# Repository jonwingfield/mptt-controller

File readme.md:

# MPTT Charge Controller

Reference Design: http://www.ti.com/tool/TIDA-00120

Better Reference Design: http://www.ti.com/lit/ug/tiduej8a/tiduej8a.pdf?&ts=1588978099192

## Resources

- How Buck Converters work (video is super helpful): https://electronicsforu.com/videos-slideshows/diy-buck-converter-tutorial
- DIY MPTT Charge Controller: http://coder-tronics.com/c2000-solar-mppt-tutorial-pt1/. This explains how to build a buck converter that is very efficient (see notes below).
- Fundamentals of MOSFET Driver circuits: http://www.ti.com/lit/ml/slua618/slua618.pdf
- Another DIY. Very mature https://hackaday.io/project/158859-high-efficiency-mppt-solar-charger
- TI Buck Converter Reference: http://www.ti.com/tool/PMP7051C http://www.ti.com/lit/ug/sluu121b/sluu121b.pdf

## Theory of Operation

### Buck Converter

The basics of a buck converter are simple and are well-explained in the above link. Use PWM and a MOSFET to reduce the average voltage. Add an inductor to smooth the current. Add a diode to create a current path when the MOSFET is off. Add a capacitor to smooth the voltage. Finally, some voltage feedback mechanism is necessary to adapt the PWM duty cycle to keep the voltage constant.

#### Component Selection (Inductor and Capacitor)

http://www.onsemi.com/pub/Collateral/AND9135-D.PDF
http://www.ti.com/lit/an/snva038b/snva038b.pdf?ts=1591102835925

#### Efficiency (see resources for overview)

Efficiency Calculation: http://www.ti.com/lit/an/slyt358/slyt358.pdf and https://www.electronicdesign.com/power/fundamentals-buck-converter-efficiency

There a few efficiency problems with the basic buck converter design:

1. The voltage drop of the diode.
2. Output ripple.
3. Switching losses in the MOSFET.

(1) is addressed by replacing the diode with a MOSFET and toggling it opposite the main MOSFET. The main MOSFET is known as the high-side and the other is the low-side. This is called a synchronous buck converter.
(2) is addressed by what's known as an *interleaved* design. This places two circuits in parallel, which supposedly halves the ripple. _TODO: understand why_.
(3) is minimized by a few factors:
1. Low RDS(on) MOSFET.
2. Low Rise/Fall time MOSFET.
3. Selection of switch frequency. A higher frequency will reduce output ripple but increase switching losses, and vise-versa.

Another important consideration is the drive current of the gate driver IC. A higher drive current will switch the MOSFET faster and result in lower switching losses. _TODO: understand why_

### Ringing

http://www.ti.com/lit/an/slpa010/slpa010.pdf

This happens at the gate of the MOSFETs. I don't fully understand why yet, even after reading the above, but it's the reason we need a gate resistor between the driver and the MOSFET.

Also, parasitic inductances and capacitances occur due to the fast switching, so an RC Snubber circuit can be used to mitigate this: http://rohmfs.rohm.com/en/products/databook/applinote/ic/power/switching_regulator/buck_snubber_app-e.pdf

Techniques to reduce ringing: http://www.ti.com/lit/an/slpa010/slpa010.pdf

## Diode Emulation Mode

When the current is low, the inductor current can go negative, resulting in lost efficiency and back current flow into the panel. To prevent this, the sync FET is kept off and uses the body diode to conduct current. This is known as diode emulation mode. 

Important: we also need to use this mode at startup to prevent issues with reverse current flow. See https://en-support.renesas.com/knowledgeBase/4967491. 

See also: http://www.ti.com/lit/ug/tiduan2/tiduan2.pdf?ts=1590949279905

## Appendix A - Notes (because I'm a noob ;)

N-Channel MOSFETs/Transistors are generally used on the ground side of a load. P-Channels on the high side, and are reversed (low = on, high = off).

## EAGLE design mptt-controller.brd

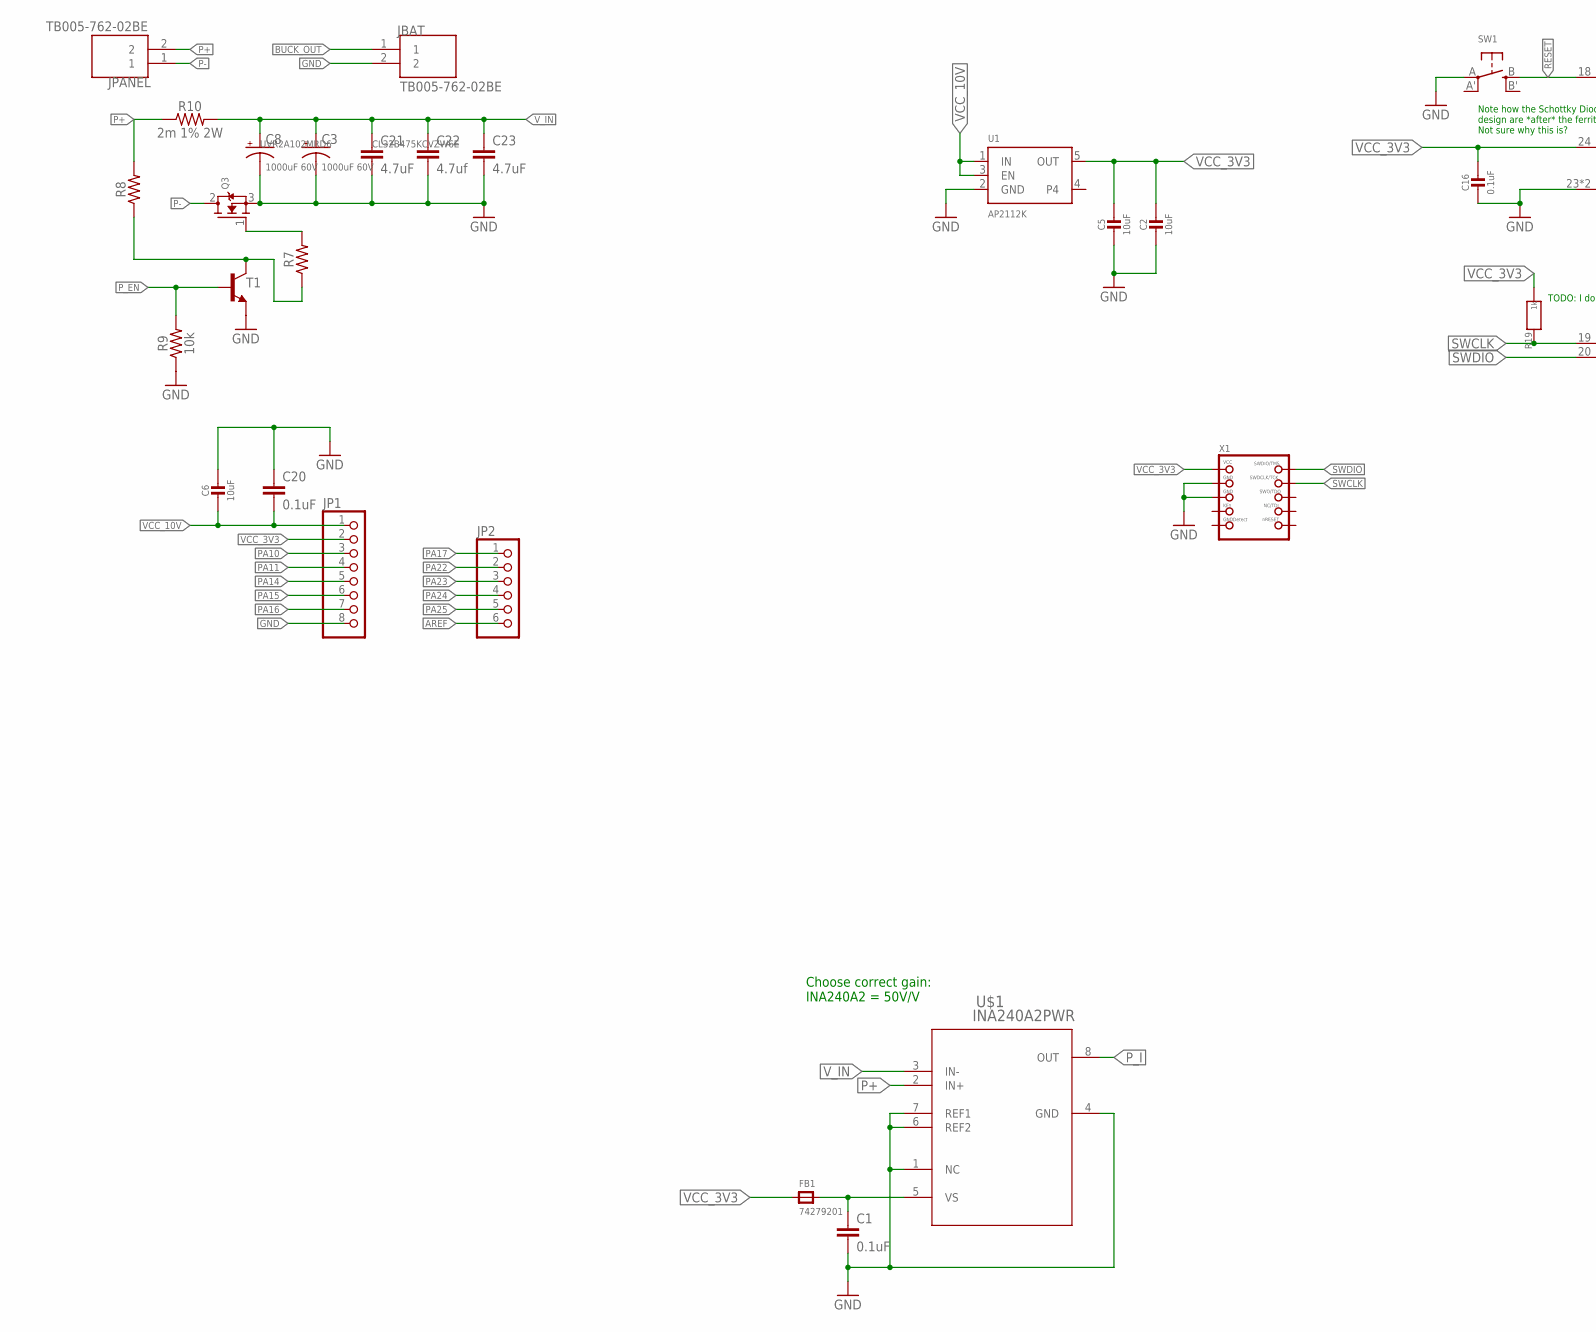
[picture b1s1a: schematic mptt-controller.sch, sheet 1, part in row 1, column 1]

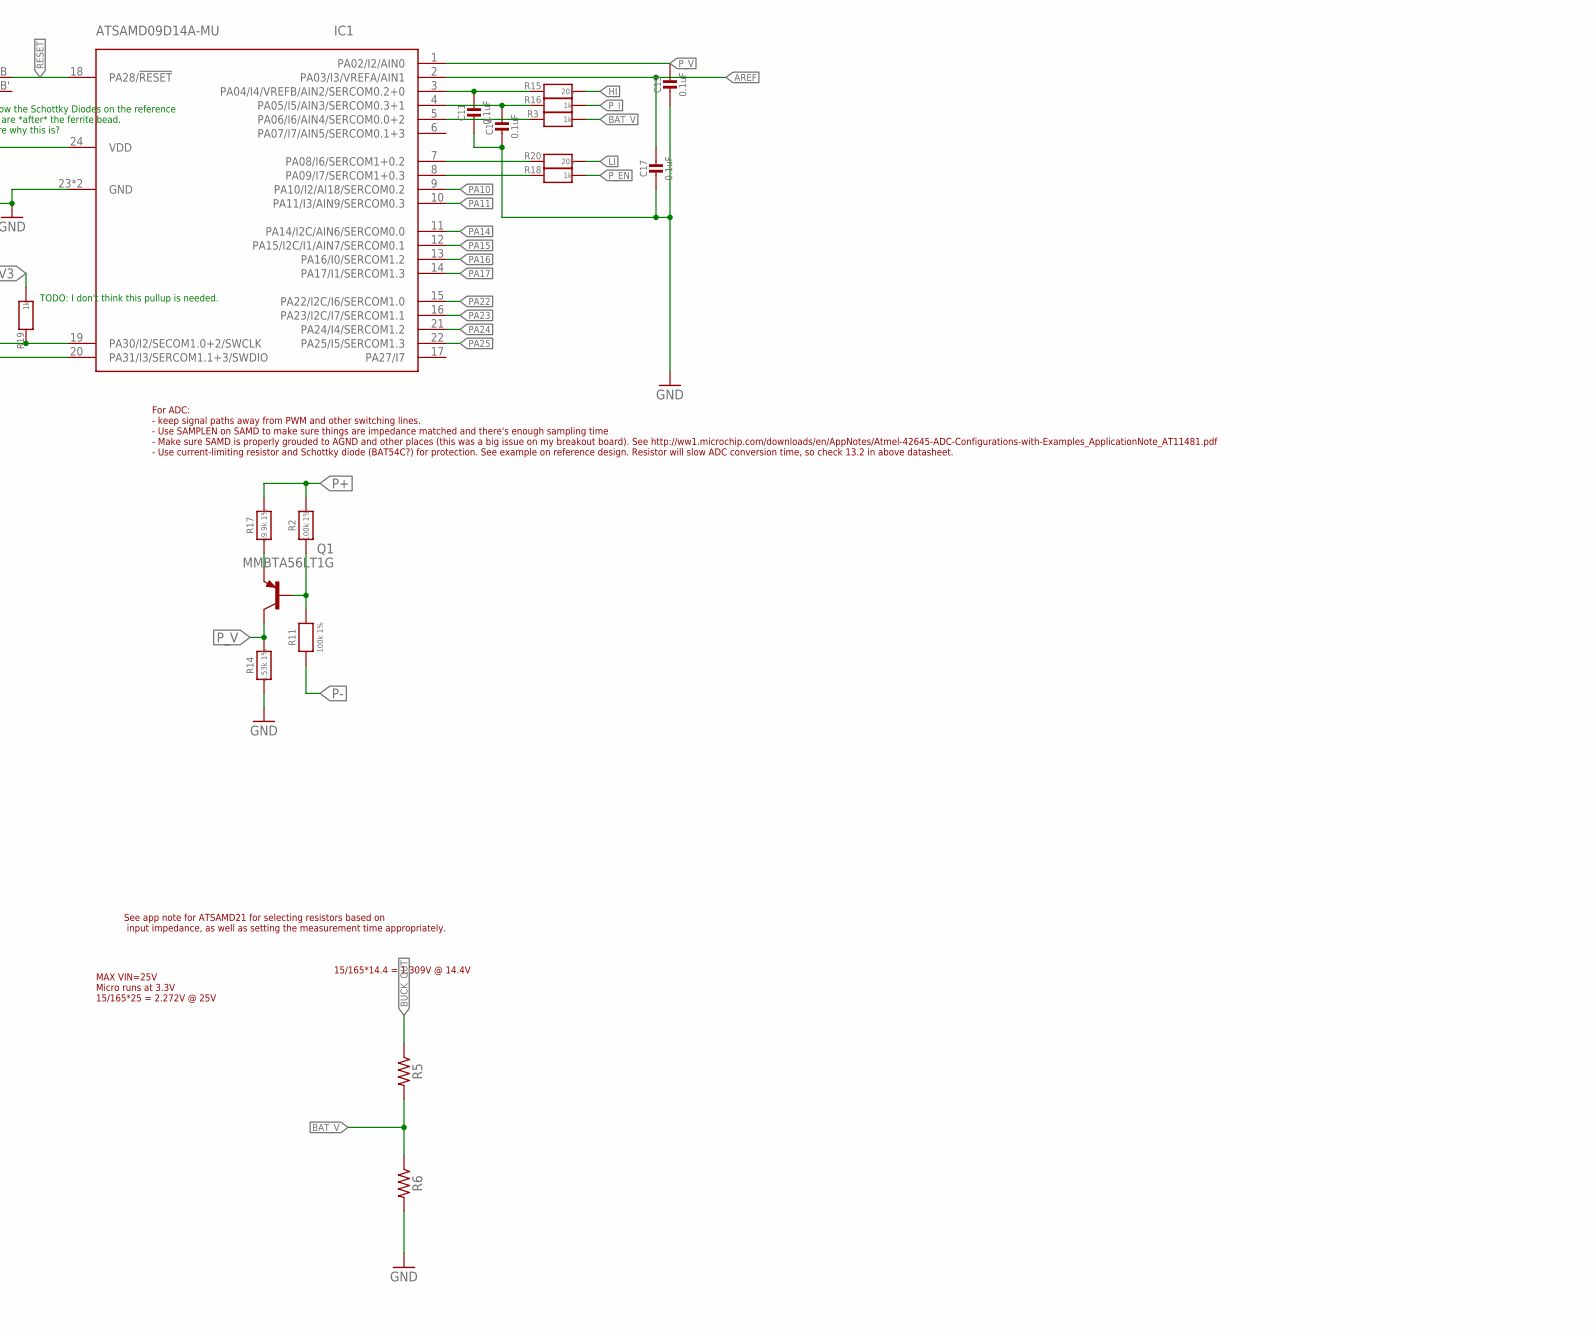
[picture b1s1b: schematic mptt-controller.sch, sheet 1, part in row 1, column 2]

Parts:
C1, C20: 0.1uF; 0603-CAP
C2, C5, C6: 10uF; _0805
C3: 1000uF 60V; CPOL-RADIAL-1000UF-25V
C8: 1000uF 60V; CPOL-RADIAL-1000UF-25V; PARTNUM UVR2A102MRD6
C11, C13, C14, C16, C17: 0.1uF; _0402MP
C21: 4.7uF; C1210; PARTNUM CL32B475KCVZW6E
C22: 4.7uf; C1210
C23: 4.7uF; C1210
FB1: 74279201; _0805
IC1: ATSAMD09D14A-MU; QFN24_4MM
JBAT: TB005-762-02BE; CUI_TB005-762-02BE
JP1: HEADER-1X8ROUND; 1X08_ROUND
JP2: HEADER-1X6ROUND; 1X06_ROUND
JPANEL: TB005-762-02BE; CUI_TB005-762-02BE
Q1: MMBTA56LT1G; SOT23-BEC
Q3: MOSFET-NGDS_TO220V; TO220V
R2, R11: 100k 1%; _0805MP
R3, R16, R18, R19: 1k; _0402MP
R5, R6, R7, R8: 0603
R9: 10k; 0603
R10: 2m 1% 2W; 2512
R14: 4.53k 1%; _0805MP
R15, R20: 205; _0402MP
R17: 49.9k 1%; _0805MP
SW1: SWITCH_TACT_SMT4.6X2.8; BTN_KMR2_4.6X2.8
T1: MMBT3904LT1-NPN-SOT23-BEC; SOT23-BEC
U1: AP2112K; SOT23-5
U$1: INA240A2PWR; PW0008A_N
X1: JTAG-CORTEXBOX; 2X05_1.27MM_BOX_NOPOSTS

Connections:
AREF: C17.1, IC1.2 (PA03/I3/VREFA/AIN1), JP2.6
BAT_V: R3.2, R5.2, R6.1
BUCK_OUT: JBAT.1, R5.1; also elsewhere on the board
GND: C1.2, C2.2, C3.-, C5.2, C6.1, C8.-, C11.2, C13.2, C14.2, C16.2, C17.2, C20.1, C21.2, C22.2, C23.2, IC1.23 (GND), IC1.THERM (GND), JBAT.2, JP1.8, Q3.3 (S), R6.2, R9.1, R14.1, SW1.A, T1.E, U1.2 (GND), U$1.1 (NC), U$1.4 (GND), U$1.6 (REF2), U$1.7 (REF1), X1.3 (GND), X1.5 (GND); also elsewhere on the board
HI: R15.2; also elsewhere on the board
LI: R20.2; also elsewhere on the board
unnamed: IC1.7 (PA08/I6/SERCOM1+0.2), R20.1
unnamed: Q3.1 (G), R7.2
unnamed: IC1.8 (PA09/I7/SERCOM1+0.3), R18.1
unnamed: Q1.B, R2.1, R11.2
unnamed: Q1.E, R17.1
unnamed: C11.1, IC1.3 (PA04/I4/VREFB/AIN2/SERCOM0.2+0), R15.1
unnamed: R7.1, R8.1, T1.C
unnamed: C14.1, IC1.4 (PA05/I5/AIN3/SERCOM0.3+1), R16.1
unnamed: IC1.5 (PA06/I6/AIN4/SERCOM0.0+2), R3.1
P+: JPANEL.2, R2.2, R8.2, R10.P$1 (1), R17.2, U$1.2 (IN+)
P-: JPANEL.1, Q3.2 (D), R11.1
PA10: IC1.9 (PA10/I2/AI18/SERCOM0.2), JP1.3
PA11: IC1.10 (PA11/I3/AIN9/SERCOM0.3), JP1.4
PA14: IC1.11 (PA14/I2C/AIN6/SERCOM0.0), JP1.5
PA15: IC1.12 (PA15/I2C/I1/AIN7/SERCOM0.1), JP1.6
PA16: IC1.13 (PA16/I0/SERCOM1.2), JP1.7
PA17: IC1.14 (PA17/I1/SERCOM1.3), JP2.1
PA22: IC1.15 (PA22/I2C/I6/SERCOM1.0), JP2.2
PA23: IC1.16 (PA23/I2C/I7/SERCOM1.1), JP2.3
PA24: IC1.21 (PA24/I4/SERCOM1.2), JP2.4
PA25: IC1.22 (PA25/I5/SERCOM1.3), JP2.5
P_EN: R9.2, R18.2, T1.B
P_I: R16.2, U$1.8 (OUT)
P_V: C13.1, IC1.1 (PA02/I2/AIN0), Q1.C, R14.2
RESET: IC1.18 (PA28/!RESET), SW1.B (S)
SWCLK: IC1.19 (PA30/I2/SECOM1.0+2/SWCLK), R19.1, X1.4 (SWDCLK)
SWDIO: IC1.20 (PA31/I3/SERCOM1.1+3/SWDIO), X1.2 (SWDIO)
VCC_3V3: C2.1, C5.1, C16.1, FB1.1, IC1.24 (VDD), JP1.2, R19.2, U1.5 (OUT), X1.1 (VCC)
VCC_10V: C6.2, C20.2, JP1.1, U1.1 (IN), U1.3 (EN); also elsewhere on the board
VS: C1.1, FB1.2, U$1.5 (VS)
V_IN: C3.+, C8.+, C21.1, C22.1, C23.1, R10.P$2 (2), U$1.3 (IN-); also elsewhere on the board

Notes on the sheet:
For ADC: - keep signal paths away from PWM and other switching lines. - Use SAMPLEN on SAMD to make sure things are impedance matched and there's enough sampling time - Make sure SAMD is properly grouded to AGND and other places (this was a big issue on my breakout board). See http://ww1.microchip.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
MAX VIN=25V Micro runs at 3.3V 15/165*25 = 2.272V @ 25V
15/165*14.4 = 1.309V @ 14.4V
See app note for ATSAMD21 for selecting resistors based on input impedance, as well as setting the measurement time appropriately.
Choose correct gain: INA240A2 = 50V/V
Note how the Schottky Diodes on the reference design are *after* the ferrite bead. Not sure why this is?
TODO: I don't think this pullup is needed.

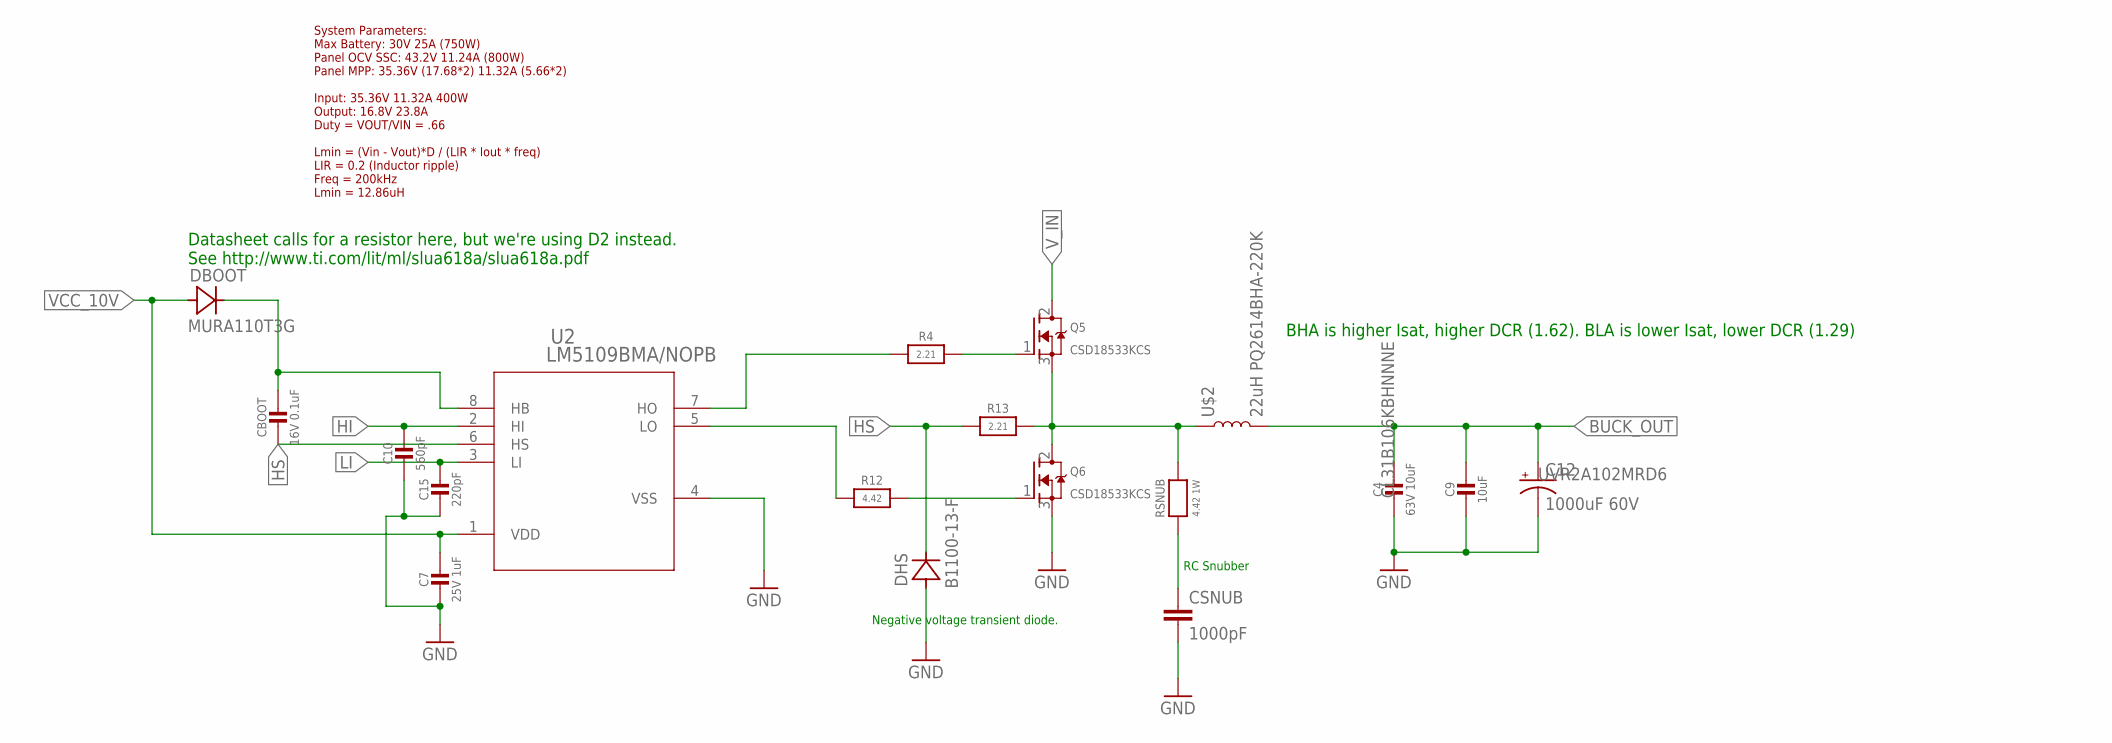
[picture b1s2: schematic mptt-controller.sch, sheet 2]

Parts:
C4: 63V 10uF; _1206
C7: 25V 1uF; _0805
C9: 10uF; _1206
C10: 560pF; _0603
C12: 1000uF 60V; CPOL-RADIAL-1000UF-25V; PARTNUM UVR2A102MRD6
C15: 220pF; _0603
CBOOT: 16V 0.1uF; _0805
CSNUB: 1000pF; 0603-CAP
DBOOT: MURA110T3G; SMA
DHS: B1100-13-F; SMA
Q5, Q6: CSD18533KCS; TO220V
R4, R13: 2.21; _0805
R12: 4.42; _0805
RSNUB: 4.42 1W; 2512
U2: LM5109BMA/NOPB; M08A_TEX
U$2: 22uH PQ2614BHA-220K; PQ2614

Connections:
BUCK_OUT: C4.1, C9.1, C12.+, U$2.P2 (2); also elsewhere on the board
GND: C4.2, C7.2, C9.2, C10.2, C12.-, C15.2, CSNUB.2, DHS.A, Q6.3 (S), U2.4 (VSS); also elsewhere on the board
HB: CBOOT.1, DBOOT.C, U2.8 (HB)
HI: C10.1, U2.2 (HI); also elsewhere on the board
HO: R4.1, U2.7 (HO)
HS: CBOOT.2, DHS.C, R13.1, U2.6 (HS)
LI: C15.1, U2.3 (LI); also elsewhere on the board
LO: R12.1, U2.5 (LO)
unnamed: Q5.1 (G), R4.2
unnamed: CSNUB.1, RSNUB.1
unnamed: Q6.1 (G), R12.2
SWITCH_NODE: Q5.3 (S), Q6.2 (D), R13.2, RSNUB.2, U$2.P1 (1)
VCC_10V: C7.1, DBOOT.A, U2.1 (VDD); also elsewhere on the board
V_IN: Q5.2 (D); also elsewhere on the board

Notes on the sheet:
RC Snubber
Datasheet calls for a resistor here, but we're using D2 instead. See http://www.ti.com/lit/ml/slua618a/slua618a.pdf
System Parameters: Max Battery: 30V 25A (750W) Panel OCV SSC: 43.2V 11.24A (800W) Panel MPP: 35.36V (17.68*2) 11.32A (5.66*2) Input: 35.36V 11.32A 400W Output: 16.8V 23.8A Duty = VOUT/VIN = .66 Lmin = (Vin - Vout)*D / (LIR * Iout * freq) LIR = 0.2 (Inductor ripple) Freq = 200kHz Lmin = 12.86uH
Negative voltage transient diode.
BHA is higher Isat, higher DCR (1.62). BLA is lower Isat, lower DCR (1.29)

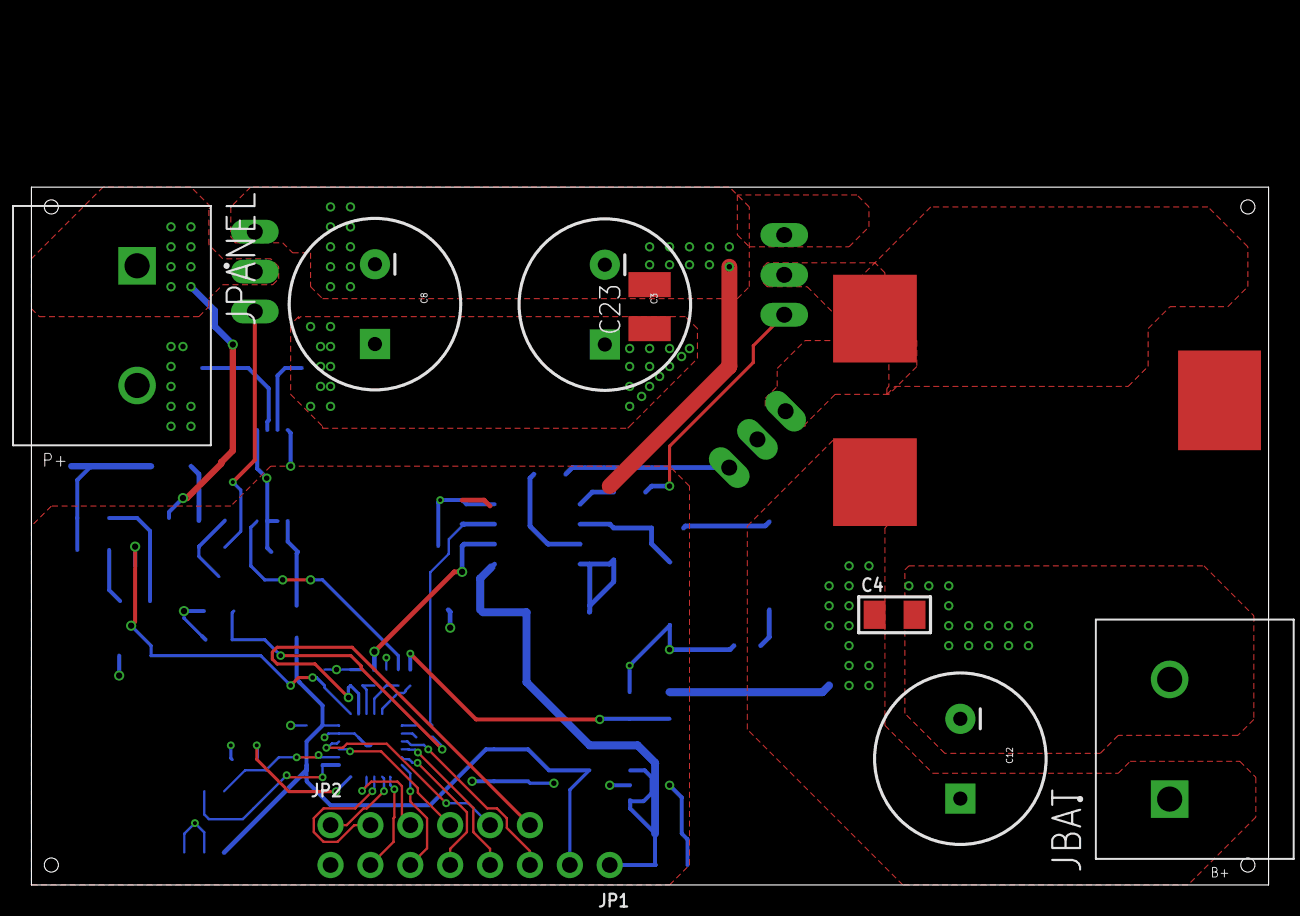
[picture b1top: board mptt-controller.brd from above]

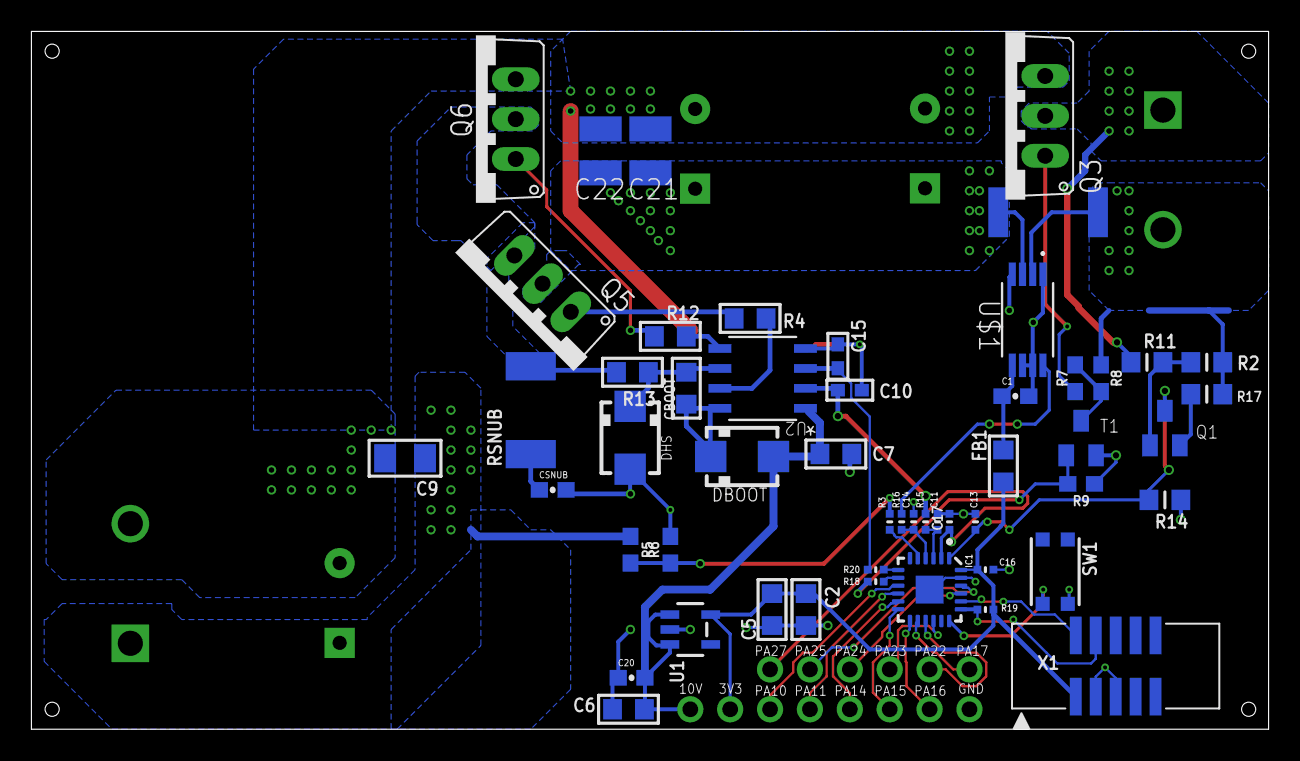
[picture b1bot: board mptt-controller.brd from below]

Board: 2 copper layers, 78.8 x 44.4 mm, 62 parts (52 on the bottom side), 45 nets.

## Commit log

2018-08-06 Add Readme
2018-08-06 Basic Notes and references
2018-08-06 Fix wrong explanation of half-bridge.
2018-08-10 Add partially finished schematic.
2020-05-08 Add better reference design
2020-05-11 Add information about snubbers.
2020-05-29 Update for new board. Getting closed to being finished.
2020-05-29 Checkpoint - More Vias and polygonal planes.
2020-05-29 Very close to being finished.
2020-05-31 Add information about diode emulation mode.
2020-06-01 Board documentation layer and add a cap for VREFA.
2020-06-02 Add more references.

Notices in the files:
parts and their libraries:
SparkFun-Resistors: Licensing: Creative Commons ShareAlike 4.0 International - https://creativecommons.org/licenses/by-sa/4.0
COPYRIGHT: Copyright (C) 2018 Accelerated Designs. All rights reserved
